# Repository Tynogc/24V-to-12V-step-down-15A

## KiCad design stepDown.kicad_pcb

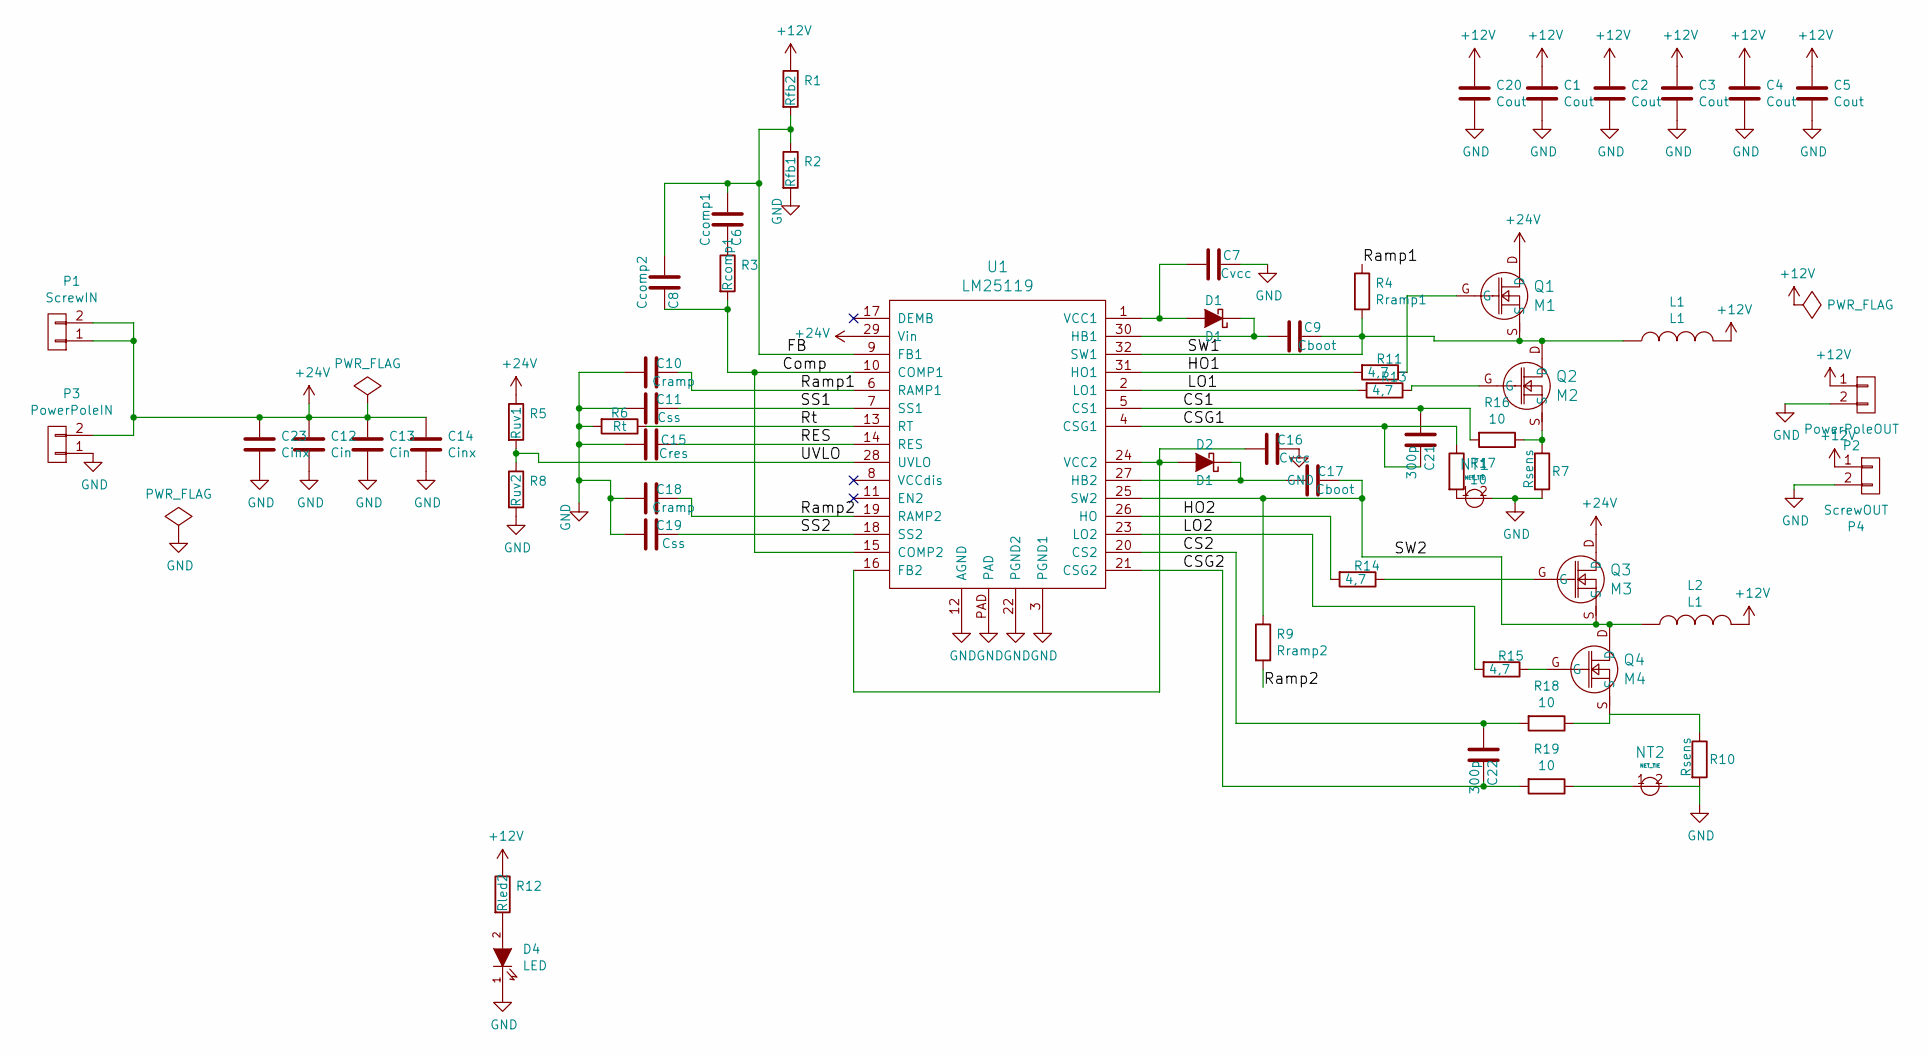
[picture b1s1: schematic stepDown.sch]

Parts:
C1, C2, C3, C4, C5, C20: Cout; C_1210
C6: Ccomp1; C_0805
C7, C16: Cvcc; C_0603
C8: Ccomp2; C_0805
C9, C17: Cboot; C_0603
C10, C18: Cramp; C_0805
C11, C19: Css; C_0805
C12, C13: Cin; C_1210
C14, C23: Cinx; C_0805
C15: Cres; C_0603
C21, C22: 300p; C_0402
D1, D2: D1; SMA_Standard
D4: LED; LED-3MM
L1, L2: L1; Z_Coilcraft_XAL7070
NT1, NT2: NET_TIE
P1: ScrewIN; Screw_Connector_5,08mm_x2
P2: PowerPoleOUT; PowerPole_1x2
P3: PowerPoleIN; PowerPole_1x2
P4: ScrewOUT; Screw_Connector_5,08mm_x2
Q1: M1; SO8_WITH_Heatpipes_New
Q2: M2; SO8_WITH_Heatpipes_New
Q3: M3; SO8_WITH_Heatpipes_New
Q4: M4; SO8_WITH_Heatpipes_New
R1: Rfb2; R_0603
R2: Rfb1; R_0603
R3: Rcomp1; R_0603
R4: Rramp1; R_0603
R5: Ruv1; R_0603
R6: Rt; R_0603
R7, R10: Rsens; R_1218
R8: Ruv2; R_0603
R9: Rramp2; R_0603
R11, R13, R14, R15: 4,7; R_0603
R12: Rled2; R_0603
R16, R17, R18, R19: 10; R_0603
U1: LM25119; WQFN32_PAD

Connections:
+12V: C1.1, C2.1, C3.1, C4.1, C5.1, C20.1, L1.2, L2.2, P2.1, P4.1, R1.1, R12.1
+24V: C12.1, C13.1, C14.1, C23.1, P1.1, P1.2, P3.2, Q1.D, Q3.D, R5.1, U1.29 (Vin)
/CS1: C21.2, R16.2, U1.5 (CS1)
/CS2: C22.2, R18.2, U1.20 (CS2)
/CSG1: C21.1, R17.1, U1.4 (CSG1)
/CSG2: C22.1, R19.2, U1.21 (CSG2)
/Comp: C8.1, R3.2, U1.10 (COMP1), U1.15 (COMP2)
/FB: C6.2, C8.2, R1.2, R2.1, U1.9 (FB1)
/HO1: R11.2, U1.31 (HO1)
/HO2: R14.2, U1.26 (HO)
/LO1: R13.2, U1.2 (LO1)
/LO2: R15.2, U1.23 (LO2)
/RES: C15.1, U1.14 (RES)
/Ramp1: C10.1, R4.1, U1.6 (RAMP1)
/Ramp2: C18.1, R9.2, U1.19 (RAMP2)
/Rt: R6.1, U1.13 (RT)
/SS1: C11.1, U1.7 (SS1)
/SS2: C19.1, U1.18 (SS2)
/SW1: C9.1, L1.1, Q1.S, Q2.D, R4.2, U1.32 (SW1)
/SW2: C17.1, L2.1, Q3.S, Q4.D, R9.1, U1.25 (SW2)
/UVLO: R5.2, R8.1, U1.28 (UVLO)
GND: C1.2, C2.2, C3.2, C4.2, C5.2, C7.1, C10.2, C11.2, C12.2, C13.2, C14.2, C15.2, C16.1, C18.2, C19.2, C20.2, C23.2, D4.1 (K), NT1.2, NT2.2, P2.2, P3.1, P4.2, R2.2, R6.2, R7.2, R8.2, R10.2, U1.3 (PGND1), U1.12 (AGND), U1.22 (PGND2), U1.PAD
unnamed: C6.1, R3.1
unnamed: C7.2, D1.2 (A), U1.1 (VCC1)
unnamed: C9.2, D1.1 (K), U1.30 (HB1)
unnamed: C16.2, D2.2 (A), U1.16 (FB2), U1.24 (VCC2)
unnamed: C17.2, D2.1 (K), U1.27 (HB2)
unnamed: D4.2 (A), R12.2
unnamed: NT1.1, R17.2
unnamed: NT2.1, R19.1
unnamed: Q1.G, R11.1
unnamed: Q2.G, R13.1
unnamed: Q2.S, R7.1, R16.1
unnamed: Q3.G, R14.1
unnamed: Q4.G, R15.1
unnamed: Q4.S, R10.1, R18.1

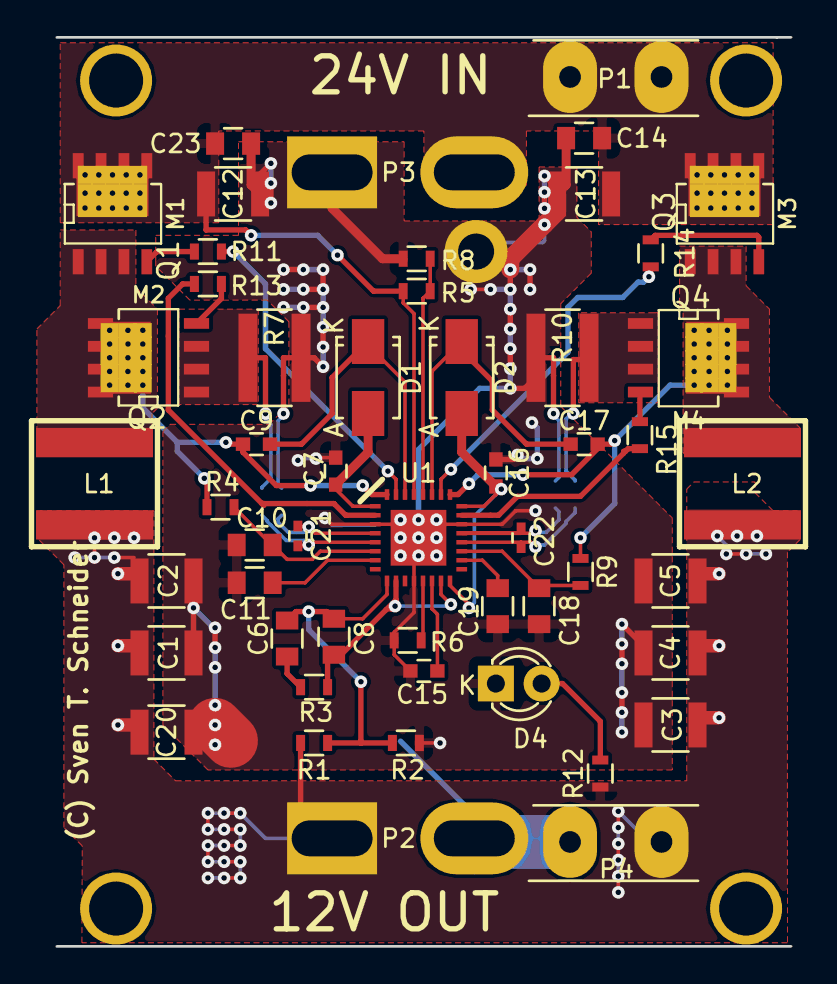
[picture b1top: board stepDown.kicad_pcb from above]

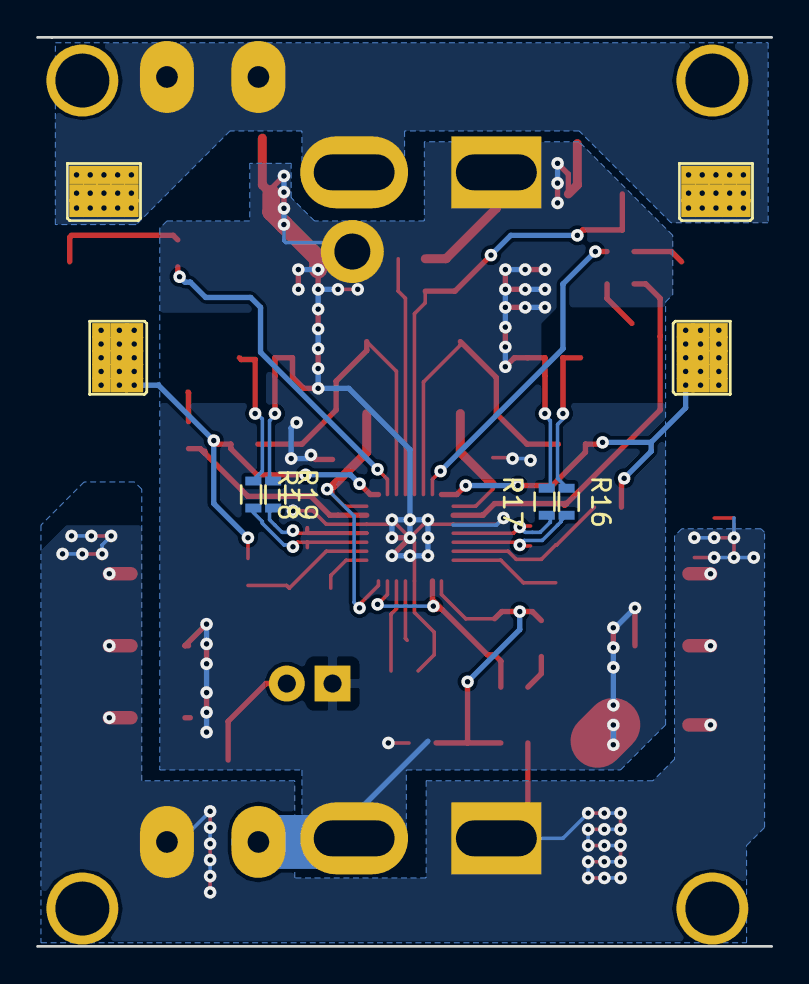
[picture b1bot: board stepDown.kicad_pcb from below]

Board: 2 copper layers, 40.8 x 50.5 mm, 58 parts (4 on the bottom side), 36 nets.

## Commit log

2016-02-04 weiter gemacht...
